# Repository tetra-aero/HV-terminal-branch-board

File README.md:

# HV-terminal-branch-board
It is board that split HV to branch and terminal.

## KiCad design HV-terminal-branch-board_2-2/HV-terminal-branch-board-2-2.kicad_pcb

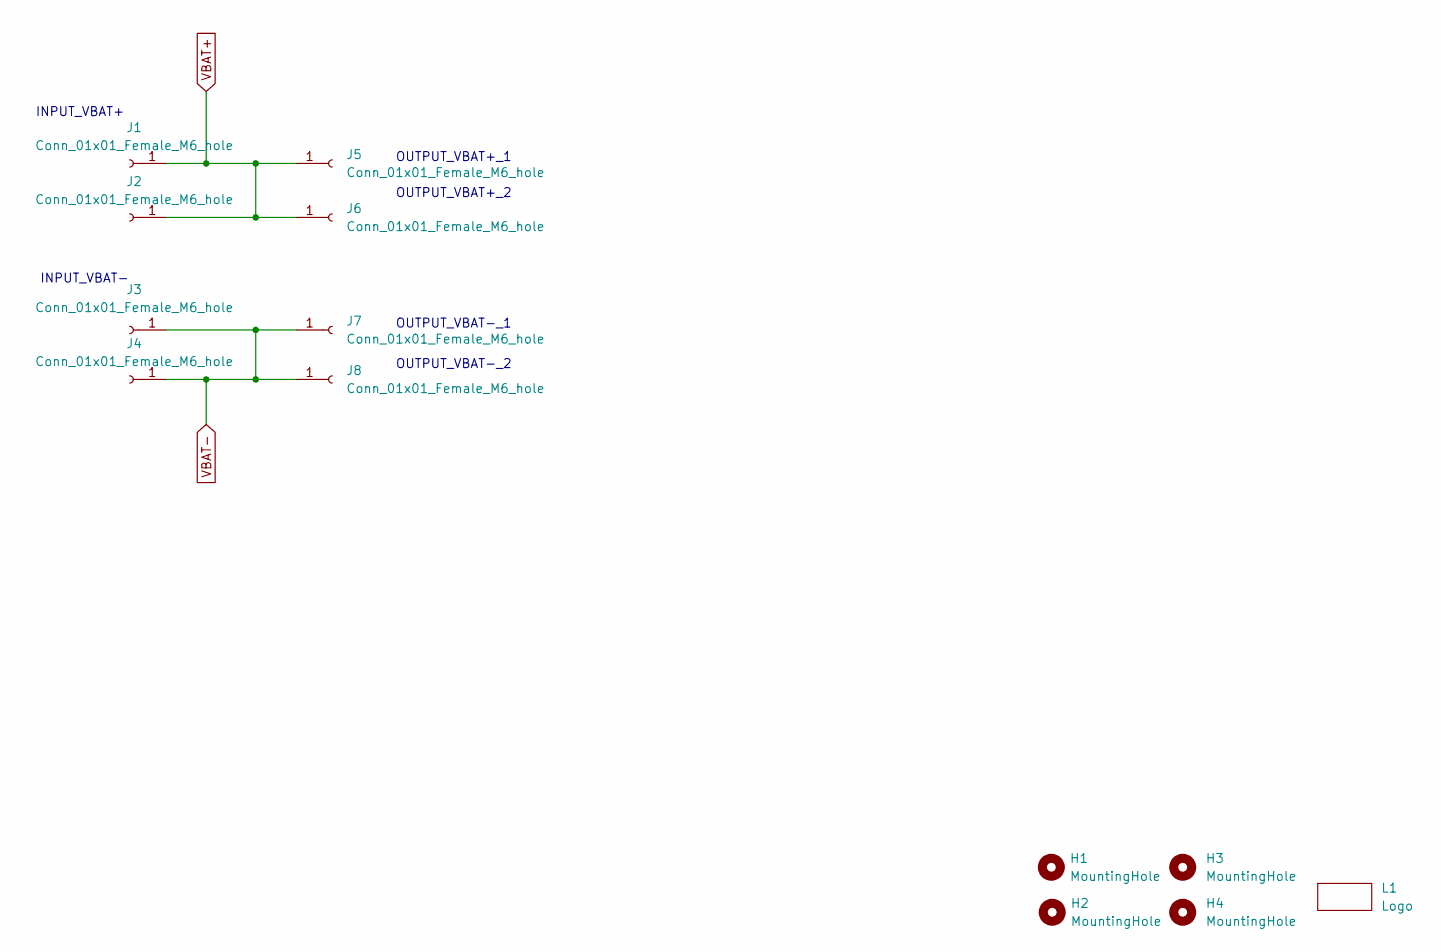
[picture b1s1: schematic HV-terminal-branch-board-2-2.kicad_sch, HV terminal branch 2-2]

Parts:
H1, H2, H3, H4: MountingHole; MountingHole_3.2mm_M3_ISO7380
J1, J2, J3, J4, J5, J6, J7, J8: Conn_01x01_Female_M6_hole; MountingHole_6.4mm_M6_Pad_TopBottom
L1: Logo; teTra-logo

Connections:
VBAT+: J1.1, J2.1, J5.1, J6.1
VBAT-: J3.1, J4.1, J7.1, J8.1

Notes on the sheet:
INPUT_VBAT-
OUTPUT_VBAT+_2
INPUT_VBAT+
OUTPUT_VBAT+_1
OUTPUT_VBAT-_2
OUTPUT_VBAT-_1

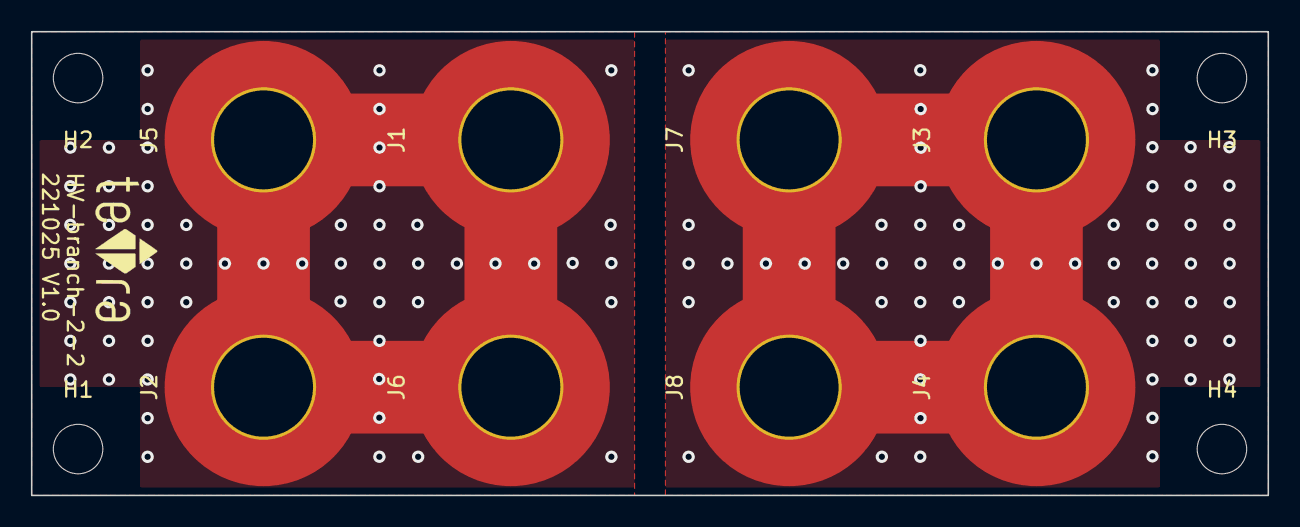
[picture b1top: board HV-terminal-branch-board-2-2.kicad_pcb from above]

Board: 2 copper layers, 80.0 x 30.0 mm, 13 parts (0 on the bottom side), 2 nets.

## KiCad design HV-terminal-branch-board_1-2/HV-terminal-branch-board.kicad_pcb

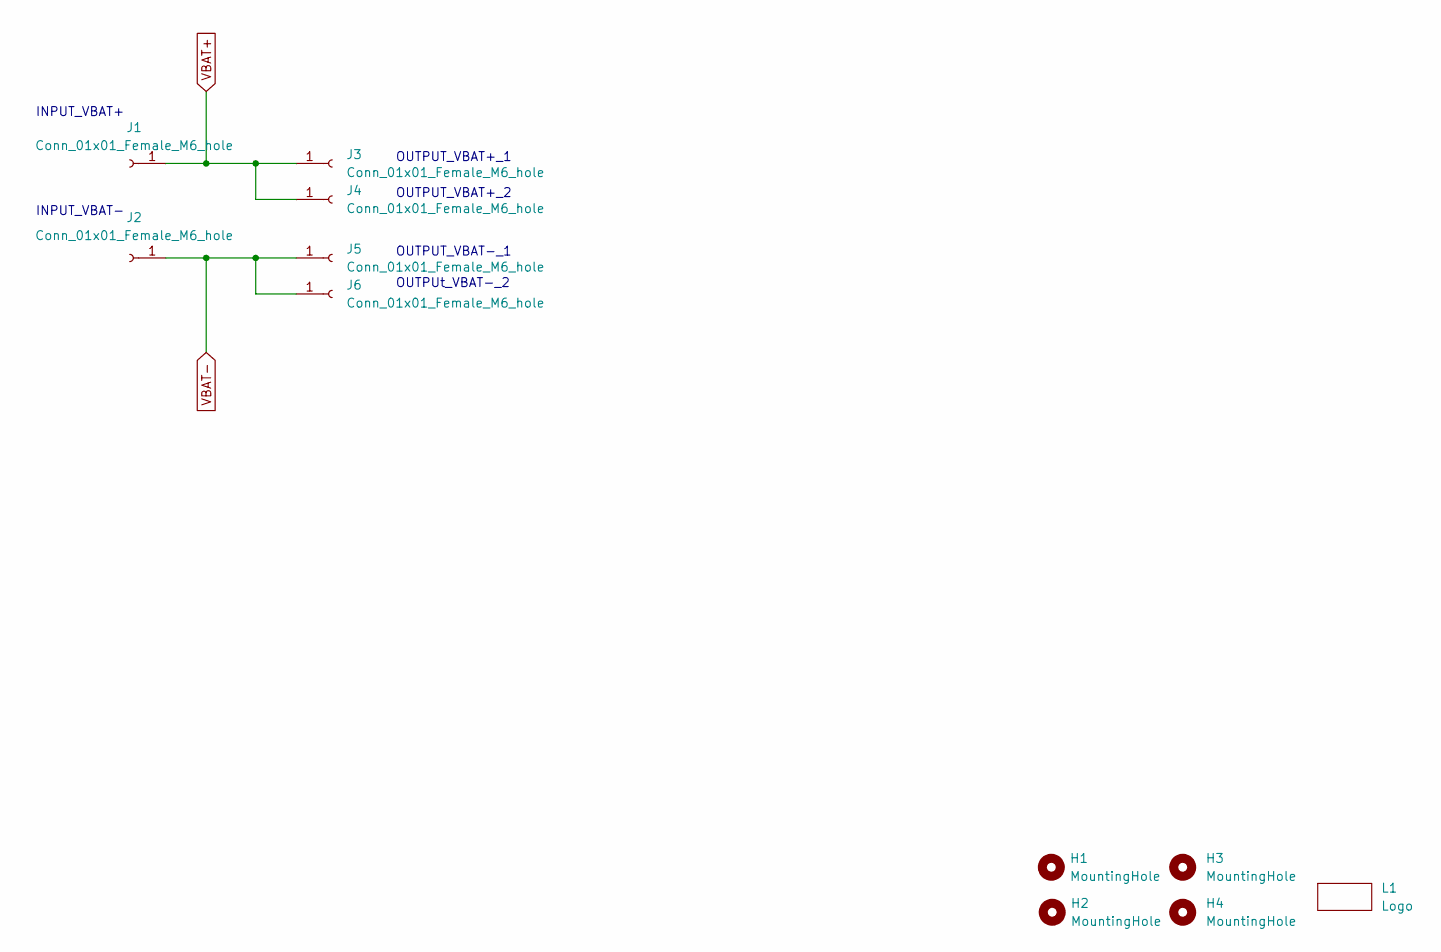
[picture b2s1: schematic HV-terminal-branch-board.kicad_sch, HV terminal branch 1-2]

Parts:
H1, H2, H3, H4: MountingHole; MountingHole_3.2mm_M3_ISO7380
J1, J2, J3, J4, J5, J6: Conn_01x01_Female_M6_hole; MountingHole_6.4mm_M6_Pad_TopBottom
L1: Logo; teTra-logo

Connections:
VBAT+: J1.1, J3.1, J4.1
VBAT-: J2.1, J5.1, J6.1

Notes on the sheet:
INPUT_VBAT-
OUTPUT_VBAT+_2
INPUT_VBAT+
OUTPUT_VBAT+_1
OUTPUt_VBAT-_2
OUTPUT_VBAT-_1

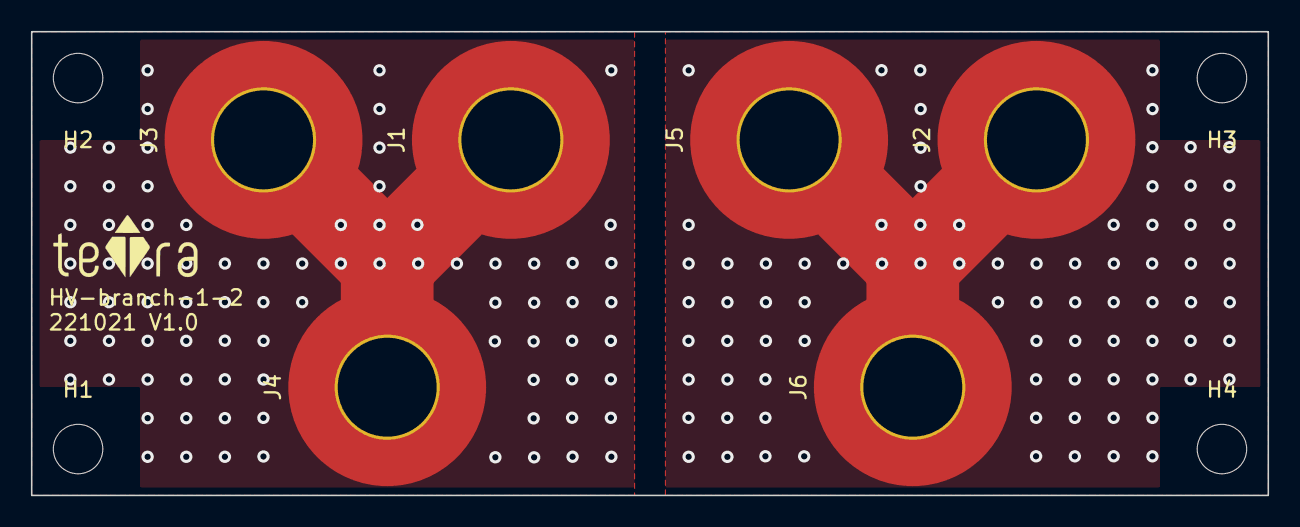
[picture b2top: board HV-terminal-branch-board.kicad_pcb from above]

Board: 2 copper layers, 80.0 x 30.0 mm, 11 parts (0 on the bottom side), 2 nets.

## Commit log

2022-10-21 add 1-2 branch
    add 1-2 branch
2022-10-21 add 2-4
    add 2-4
2022-10-26 add 2-2
    add 2-2
2022-10-26 add 2-2-half
    add 2-2-half
